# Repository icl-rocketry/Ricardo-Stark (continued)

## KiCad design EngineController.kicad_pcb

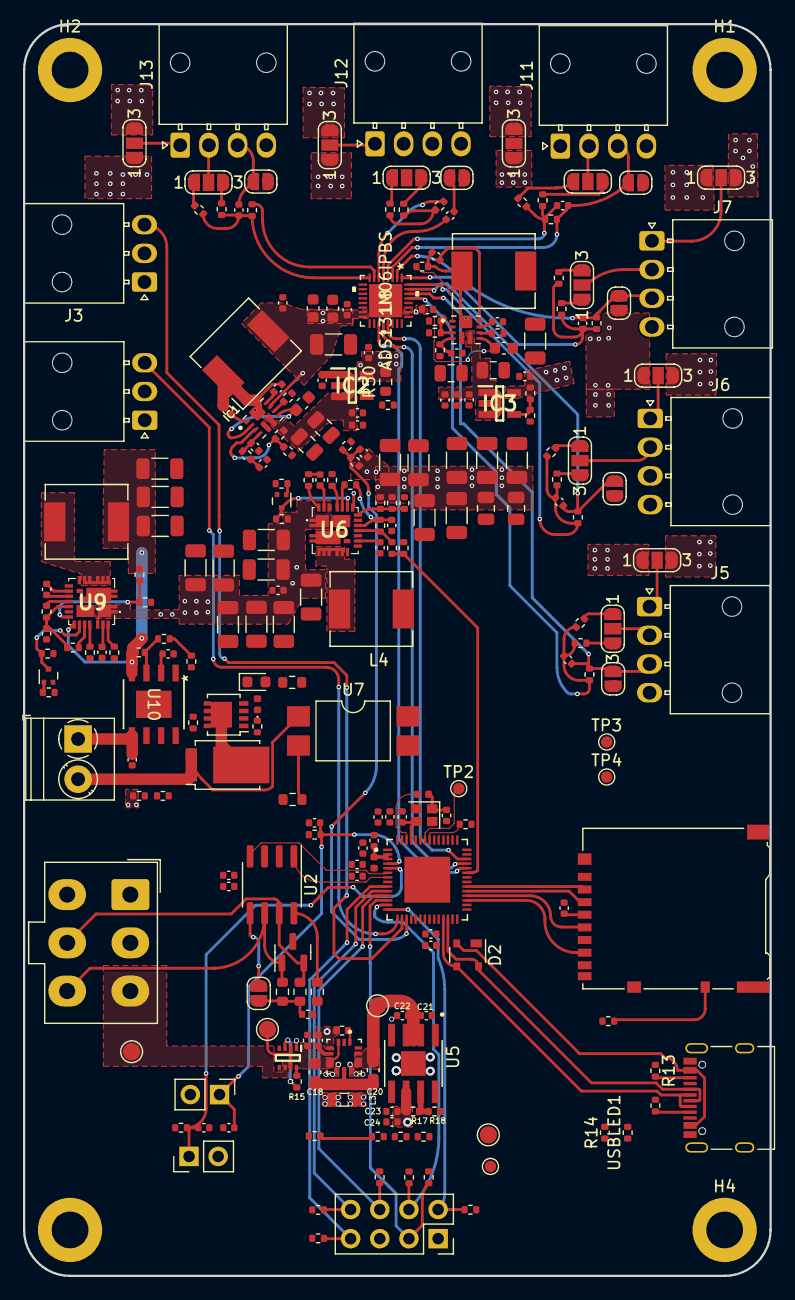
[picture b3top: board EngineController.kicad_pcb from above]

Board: 4 copper layers, 65.0 x 109.0 mm, 251 parts (0 on the bottom side), 150 nets.

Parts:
3V3LED1: BLUE_LED; R_0402_1005Metric
12VLED1: RED_LED; R_0402_1005Metric
BOOTJUMPER1: Conn_01x02_Male; PinHeader_1x02_P2.54mm_Vertical
C1, C15, C17, C21, C23, C66, C74: 10uF; C_0402_1005Metric
C2, C4, C7, C19, C25, C59, C68, C69, C71, C72: 1uF; C_0402_1005Metric
C3, C5, C6, C8, C10, C11, C24, C35, C46, C47, C91: 0.1uF; C_0402_1005Metric
C9, C48, C50, C51, C53, C54, C55: 10nF; C_0402_1005Metric
C12, C13: 11pF; C_0402_1005Metric
C14, C34, C62, C64, C67, C75, C80, C81: 100nF; C_0402_1005Metric
C16: 47nF; C_0402_1005Metric
C18, C49, C76: 10uF; C_0603_1608Metric
C20: 22uF; C_0603_1608Metric
C22, C26, C70: 4.7uF; C_0402_1005Metric
C27, C28, C29, C31, C33, C65, C85, C87, C89: 47uF; C_1206_3216Metric
C30, C32, C36, C38, C39, C40, C42, C43, C44, C45: DNP; C_1206_3216Metric
C37, C41: DNP; C_0805_2012Metric
C52: 100nF; C_0603_1608Metric
C56: 2.2uF; C_0603_1608Metric
C57: 180pF; C_0402_1005Metric
C58: 4.7nF; C_0402_1005Metric
C60, C61, C79: 22uF; C_0805_2012Metric
C63, C73: 2.2uF; C_0402_1005Metric
C77: 120pF; C_0402_1005Metric
C78: 2.2nF; C_0805_2012Metric
C82: 22uF; C_1206_3216Metric
C92: 2.2nF; C_0402_1005Metric
C93: 100uF; C_0402_1005Metric
D1: SM712_SOT23; SOT-23
D2: SP0503BAHT; SOT-143
D4: DST1550S; TO-277B
D6: RED_LED; LED_0603_1608Metric
ENJUMPER1: Conn_01x02_Male; PinHeader_1x02_P2.54mm_Vertical
Firing1: EMERALD_LED; LED_0402_1005Metric
H1, H2, H3, H4: MountingHole_Pad; MountingHole_3.2mm_M3_DIN965_Pad
IC1, IC4: TPS61089RNRR; IC_TPS61089RNRR
IC2, IC3: AP2205-W5-7; SOT95P282X145-5N
J1: RBUS; Molex_Mini-Fit_Jr_5566-06A_2x03_P4.20mm_Vertical
J2: USB_C_Receptacle_USB2.0; USB_C_Receptacle_Palconn_UTC16-G
J3: ServoCH1; Molex_Nano-Fit_105313-xx03_1x03_P2.50mm_Horizontal
J4: ServoCH2; Molex_Nano-Fit_105313-xx03_1x03_P2.50mm_Horizontal
J5, J6, J7, J11, J12, J13: 1053131104; Molex_Nano-Fit_105313-xx04_1x04_P2.50mm_Horizontal
J8: GPIO Breakout; PinSocket_2x04_P2.54mm_Vertical
J9: Micro_SD_Card_Det; microSD_HC_Hirose_DM3AT-SF-PEJM5
J10: Conn_01x02_Male; TerminalBlock_Phoenix_PT-1,5-2-3.5-H_1x02_P3.50mm_Horizontal
JP1: TermJP; SolderJumper-2_P1.3mm_Open_RoundedPad1.0x1.5mm
JP2, JP4, JP5, JP7, JP8, JP10, JP11, JP13, JP14, JP16, JP17, JP19: SolderJumper_3_Open; SolderJumper-3_P1.3mm_Open_RoundedPad1.0x1.5mm_NumberLabels
JP3, JP6, JP9, JP12, JP15, JP18: SolderJumper_2_Open; SolderJumper-2_P1.3mm_Open_RoundedPad1.0x1.5mm
L1: 2.0nH; L_0402_1005Metric
L2: 20nH; L_0402_1005Metric
L3: 1uH; L_0805_2012Metric
L4, L7: 3.3uH; IND_SRP6540-390M
L5, L6: SRR6038-5R0Y; IND_SRP6540-390M
Q1, Q3: SSM3K15AMFV,L3F; SOT-723
Q2: BUK9M11-40EX; LFPAK33
R1, R3: 10K; R_0402_1005Metric
R2, R4, R29: 470; R_0402_1005Metric
R5: 499R; R_0402_1005Metric
R6: 3k; R_0402_1005Metric
R7, R28: 1.5k; R_0402_1005Metric
R8: 2.2k; R_0402_1005Metric
R9: 0; R_0603_1608Metric
R10, R11: 60; R_0603_1608Metric
R12, R13, R14: 5.1k; R_0402_1005Metric
R15, R18, R19, R21, R27, R32, R35, R38, R41, R44, R47, R54, R57, R66, R67, R75, R86: 10k; R_0402_1005Metric
R16: 14k; R_0402_1005Metric
R17: 56k; R_0402_1005Metric
R20: 130k; R_0402_1005Metric
R22, R69: 2.2; R_0402_1005Metric
R23: 294k; R_0402_1005Metric
R24, R72: 1k; R_0402_1005Metric
R25, R73: 200k; R_0402_1005Metric
R26, R74: 100k; R_0402_1005Metric
R30, R33, R36, R39, R42, R52: 90k; R_0402_1005Metric
R31, R34, R37, R40, R43, R53: 31.7k; R_0402_1005Metric
R45: 17.4k; R_0402_1005Metric
R46: 1K; R_0402_1005Metric
R48: 127k; R_0402_1005Metric
R49: 50k; R_0402_1005Metric
R50: 152k; R_0603_1608Metric
R51: 301k; R_0402_1005Metric
R55: 51k; R_0402_1005Metric
R56: 0k; R_0402_1005Metric
R58: 190k; R_0402_1005Metric
R59, R60, R61, R62, R63, R64: DNP; R_0402_1005Metric
R65: 120; R_0402_1005Metric
R68: 120; R_0603_1608Metric
R70: 10k; R_0603_1608Metric
R76: 464K; R_0402_1005Metric
R77: 33.2K; R_0402_1005Metric
R78: 47.5K; R_0402_1005Metric
R79: 453; R_0402_1005Metric
R84: 18.7k; R_0402_1005Metric
R85: 2k; R_0402_1005Metric
R87: 475k; R_0402_1005Metric
R88: 287k; R_0402_1005Metric
TP1, TP2, TP3, TP4: TestPoint; TestPoint_Pad_D1.0mm
TP5, TP6, TP7, TP8: TestPoint; TestPoint_Pad_D1.5mm
TXLED1: GREEN_LED; R_0402_1005Metric
U1: ESP32-S3; QFN40P700X700X90-57N
U2: SN65HVD230; SOIC-8_3.9x4.9mm_P1.27mm
U3: LM66200DRLR; SOTFL50P160X60-8N
U4: MAX77827AEFD+T; CONV_MAX77827AEFD+T
U5: SC4215; SOIC127P599X175-9N
U6, U9: SiC437BED-T1-GE3; SiC437BEDT1GE3
U7: LTV-247; SMDIP-4_W9.53mm
U8: ADS131M06IPBS; ADS131M06IRSNR
U10: TPS259621DDAT; SO-PP-DDA-8_TEX
USBLED1: WHITE_LED; R_0402_1005Metric
Y1: R940000171; Crystal_SMD_2016-4Pin_2.0x1.6mm

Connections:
+3.3V: C1.1, C4.1, C5.1, C7.1, C9.1, C10.1, C11.1, C14.1, C15.1, C23.2, C24.2, C47.1, C49.1, C52.1, C64.1, C65.1, C71.1, C72.2, C81.1, C82.1, IC1.9 (VIN), IC4.9 (VIN), J8.5, J9.4 (VDD), L1.1, L5.1, L6.1, R1.1, R2.1, R3.1, R4.2, R17.1, R59.1, R60.1, R61.1, R62.1, R63.1, R64.1, R66.1, TP7.1, U1.20 (VDD3P3_RTC), U1.46 (VDD3P3_CPU), U1.55 (VDDA), U1.56 (VDDA), U2.3 (VCC), U5.6 (VOUT), U7.16, U8.15 (AVDD), U8.16 (SYNC/RESET), U8.26 (DVDD)
+5V: C63.1, IC2.5 (VOUT), JP4.1 (A), JP7.1 (A), JP10.1 (A), JP13.1 (A), JP16.1 (A), JP19.1 (A), R50.2
+6V: C29.1, C31.1, C33.1, C37.1, C39.1, C41.1, C43.1, C44.1, C45.1, C46.1, J3.2, J4.2, L4.1, R20.2, R23.2, R28.2, U6.18 (V_OUT)
+12V: C27.1, C28.1, C30.1, C32.1, C34.1, C36.1, C38.1, C40.1, C42.1, C73.1, IC3.5 (VOUT), J1.4, JP4.3 (B), JP7.3 (B), JP10.3 (B), JP13.3 (B), JP16.3 (B), JP19.3 (B), R6.1, R27.2, R56.2, U6.1 (V_IN_1), U6.2 (V_IN_2), U6.22 (VIN_1), U6.26 (VIN_2), U9.1 (V_IN_1), U9.2 (V_IN_2), U9.22 (VIN_1), U9.26 (VIN_2)
/ADS_CLK: U1.24 (GPIO18/ADC2_CH7/DAC_1), U8.23 (XTAL1/CLKIN)
/ADS_CS0: U1.27 (GPIO21), U8.17 (CS)
/BOOT: BOOTJUMPER1.1, C8.1, R3.2, U1.5 (GPIO0/BOOT)
/Boosts/FB_5V: IC1.3 (FB), R46.1, R47.2
/Boosts/FB_10V: IC4.3 (FB), R85.1, R86.2
/Boosts/LDO5.5V_IN: C59.1, C60.1, C61.1, C66.1, C67.1, IC1.6 (VOUT), IC2.1 (VIN), IC2.3 (EN), R46.2
/Boosts/LDO12V_IN: C69.1, C74.1, C75.1, C79.1, IC3.1 (VIN), IC3.3 (EN), IC4.6 (VOUT), R85.2
/Boosts/SW_5V: IC1.1 (FSW), R51.1
/Boosts/SW_10V: IC4.1 (FSW), R88.1
/BuckPGOOD: R7.1, R8.2, U1.37 (SPICLK_P/GPIO47)
/CAN+: D1.2 (A2), J1.5, R10.1, U2.7 (CANH)
/CAN-: D1.1 (A1), J1.6, R11.2, U2.6 (CANL)
/CAN-BUS/Vref: JP1.1 (A), U2.5 (Vref)
/CAN_RX: U1.6 (GPIO1/ADC1_CH0), U2.4 (R)
/CAN_TX: U1.7 (GPIO2/ADC1_CH1), U2.1 (D)
/CHIP_PU: C2.1, C3.1, ENJUMPER1.1, R1.2, U1.4 (CHIP_PU/RESET)
/Data+: D2.4 (K), J2.A6 (D+), J2.B6 (D+), TP4.1, U1.26 (GPIO20/USB_D+/ADC2_CH9)
/Data-: D2.3 (K), J2.A7 (D-), J2.B7 (D-), TP3.1, U1.25 (GPIO19/USB_D-/ADC2_CH8)
/HSPI_MISO: U1.39 (GPIO34), U8.20 (DOUT)
/HSPI_MOSI: U1.40 (GPIO35), U8.21 (DIN)
/HSPI_SCLK: U1.38 (GPIO33), U8.19 (SCLK)
/Power/BBIN: C17.1, C18.1, TP5.1, U3.2 (VOUT_1), U3.7 (VOUT_2), U4.3 (EN), U4.6 (IN)
/Power/BBOUT: C20.1, C21.1, C22.1, TP8.1, U4.11 (OUT), U4.13 (OUTS), U5.2 (EN), U5.3 (VIN)
/Power/BIAS: C19.1, U4.5 (BIAS)
/Power/FBIn: R17.2, R18.1, U5.7 (ADJ)
/Power/LX1: L3.1, U4.8 (LX1)
/Power/LX2: L3.2, U4.10 (LX2)
/Power/SEL: R16.1, U4.1 (SEL)
/Pyro/BOOT: C91.1, U9.23 (BOOT)
/Pyro/BUCKP_EN: Q3.1 (G), R72.2
/Pyro/Cont1: R68.1, U7.15
/Pyro/EFuse_In: C85.1, C87.1, C89.1, L7.1, R58.2, R76.2, U9.18 (V_OUT), U10.4 (IN)
/Pyro/EN: Q3.3 (D), R75.1, U9.19 (EN)
/Pyro/FB: R58.1, R67.2, U9.17 (FB)
/Pyro/Nuke 1: Firing1.2 (A), Q2.4 (G)
/Pyro/PGOOD: R57.2, U9.14 (P_GOOD)
/Pyro/PHASE: R69.1, U9.24 (PHASE)
/Pyro/PyroV: C93.2, J10.1, U10.5 (OUT)
/Pyro/SW: L7.2, U9.5 (SW_1), U9.6 (SW_2), U9.7 (SW_3), U9.8 (SW_4), U9.9 (SW_5), U9.30 (SW_6)
/Pyro/VDD: C68.2, R57.1, R73.2, U9.15 (VDD)
/RXD: TP2.1, U1.50 (U0RXD/PROG/GPIO44)
/Servo1PWM: J3.3, U1.16 (GPIO11/ADC2_CH0)
/Servo2PWM: J4.3, U1.15 (GPIO10/ADC1_CH9)
/ServoV_LOG: C46.2, R28.1, R29.2, U1.17 (GPIO12/ADC2_CH1)
/TXD: R5.1, TP1.1, TXLED1.1 (K)
/actuators/GPIO0: J8.2, R59.2, U1.14 (GPIO9/ADC1_CH8)
/actuators/GPIO1: J8.3, R60.2, U1.12 (GPIO7/ADC1_CH6)
/actuators/GPIO2: J8.4, R61.2, U1.13 (GPIO8/ADC1_CH7)
/actuators/GPIO3: J8.6, R62.2, U1.11 (GPIO6/ADC1_CH5)
/actuators/GPIO4: J8.7, R63.2, U1.9 (GPIO4/ADC1_CH3)
/actuators/GPIO5: J8.8, R64.2, U1.10 (GPIO5/ADC1_CH4)
/buckC/BOOT: C35.1, U6.23 (BOOT)
/buckC/BUCKC_EN: Q1.1 (G), R24.2, U1.18 (GPIO13/ADC2_CH2)
/buckC/EN: Q1.3 (D), R27.1, U6.19 (EN)
/buckC/FB: R20.1, R21.2, R23.1, U6.17 (FB)
/buckC/PGOOD: R7.2, R19.2, U6.14 (P_GOOD)
/buckC/PHASE: R22.1, U6.24 (PHASE)
/buckC/SW: L4.2, U6.5 (SW_1), U6.6 (SW_2), U6.7 (SW_3), U6.8 (SW_4), U6.9 (SW_5), U6.30 (SW_6)
/buckC/VDD: C25.2, R19.1, R25.2, U6.15 (VDD)
/microSD/SD1_DET: J9.10 (DET_A), R66.2
/microSD/VSPI_MISO: J9.7 (DAT0), U1.31 (SPIWP/GPIO28)
/microSD/VSPI_SCLK: J9.5 (CLK), U1.32 (SPICS0/GPIO29)
/pressure_sensor/AIN0N: C48.2, J5.3, JP3.2 (B), R32.2, U8.30 (AIM0N)
/pressure_sensor/AIN0P: C48.1, R30.2, R31.2, R32.1, U8.29 (AIN0P)
/pressure_sensor/AIN1N: C50.2, J6.3, JP6.2 (B), R35.2, U8.31 (AIN1N)
/pressure_sensor/AIN1P: C50.1, R33.2, R34.2, R35.1, U8.32 (AIN1P)
/pressure_sensor/AIN2N: C51.2, J7.3, JP9.2 (B), R38.2, U8.2 (AIN2N)
/pressure_sensor/AIN2P: C51.1, R36.2, R37.2, R38.1, U8.1 (AIN2P)
/pressure_sensor/AIN3N: C53.2, J11.3, JP12.2 (B), R41.2, U8.3 (AIN3N)
/pressure_sensor/AIN3P: C53.1, R39.2, R40.2, R41.1, U8.4 (AIN3P)
/pressure_sensor/AIN4N: C54.2, J12.3, JP15.2 (B), R44.2, U8.6 (AIN4N)
/pressure_sensor/AIN4P: C54.1, R42.2, R43.2, R44.1, U8.5 (AIN4P)
/pressure_sensor/AIN5N: C55.2, J13.3, JP18.2 (B), R54.2, U8.7 (AIN5N)
/pressure_sensor/AIN5P: C55.1, R52.2, R53.2, R54.1, U8.8 (AIN5P)
GND: 3V3LED1.1 (K), 12VLED1.1 (K), BOOTJUMPER1.2, C1.2, C2.2, C3.2, C4.2, C5.2, C6.2, C7.2, C8.2, C9.2, C10.2, C11.2, C12.2, C13.2, C14.2, C15.2, C16.2, C17.2, C18.2, C19.2, C20.2, C21.2, C22.2, C23.1, C24.1, C25.1, C26.1, C27.2, C28.2, C29.2, C30.2, C31.2, C32.2, C33.2, C34.2, C36.2, C37.2, C38.2, C39.2, C40.2, C41.2, C42.2, C43.2, C44.2, C45.2, C47.2, C49.2, C52.2, C56.2, C57.2, C58.2, C59.2, C60.2, C61.2, C63.2, C64.2, C65.2, C66.2, C67.2, C68.1, C69.2, C70.1, C71.2, C72.1, C73.2, C74.2, C75.2, C76.2, C77.2, C78.2, C79.2, C81.2, C82.2, C85.2, C87.2, C89.2, C92.1, C93.1, D1.3 (common), D2.1 (A), D6.1 (K), ENJUMPER1.2, H1.1, H2.1, H3.1, H4.1, IC1.5 (GND), IC2.2 (GND), IC3.2 (GND), IC4.5 (GND), J1.1, J1.2, J2.A1 (GND), J2.A12 (GND), J2.B1 (GND), J2.B12 (GND), J2.S1 (SHIELD), J3.1, J4.1, J5.4, J6.4, J7.4, J8.1, J9.6 (VSS), J9.9 (DET_B), J9.11 (SHIELD), J11.4, J12.4, J13.4, JP3.1 (A), JP6.1 (A), JP9.1 (A), JP12.1 (A), JP15.1 (A), JP18.1 (A), Q1.2 (S), Q2.1 (S), Q2.2 (S), Q2.3 (S), Q3.2 (S), R8.1, R9.2, R12.2, R13.1, R16.2, R18.2, R21.1, R24.1, R26.2, R29.1, R47.1, R48.1, R49.1, R55.1, R65.2, R67.1, R70.2, R72.1, R74.2, R78.2, R86.1, R87.1, U1.57 (GND), U2.2 (GND), U3.1 (GND_1), U3.4 (~ON), U3.5 (GND_2), U4.4 (AGND), U4.9 (PGND), U5.8 (GND), U5.9 (GND), U6.3 (P_GND_1), U6.4 (P_GND_2), U6.13 (P_GND_3), U6.16 (A_GND), U6.25 (AGND), U6.27 (PGND), U6.29 (P_GND_4), U8.13 (AGND), U8.25 (DGND), U9.3 (P_GND_1), U9.4 (P_GND_2), U9.13 (P_GND_3), U9.16 (A_GND), U9.25 (AGND), U9.27 (PGND), U9.29 (P_GND_4), U10.1 (GND), U10.EPAD (GND), USBLED1.1 (K), Y1.2, Y1.4
unnamed: 3V3LED1.2 (A), R4.1
unnamed: 12VLED1.2 (A), R6.2
unnamed: C6.1, L1.2, U1.2 (VDD3P3), U1.3 (VDD3P3)
unnamed: C13.1, L2.2, Y1.1
unnamed: C35.2, R22.2
unnamed: C58.1, R45.2
unnamed: C78.1, R84.2
unnamed: C91.2, R69.2
unnamed: D4.3 (K), Q2.5 (D)
unnamed: D6.2 (A), R68.2
unnamed: Firing1.1 (K), R65.1
unnamed: C62.1, IC1.10 (BOOT)
unnamed: C57.1, IC1.4 (COMP), R45.1
unnamed: C56.1, IC1.2 (VCC), IC1.7 (EN)
unnamed: IC1.8 (ILIM), R48.2
unnamed: C62.2, IC1.11 (SW), L5.2, R51.2
unnamed: IC2.4 (ADJ/NC), R49.2, R50.1
unnamed: IC3.4 (ADJ/NC), R55.2, R56.1
unnamed: C80.1, IC4.10 (BOOT)
unnamed: C77.1, IC4.4 (COMP), R84.1
unnamed: C76.1, IC4.2 (VCC), IC4.7 (EN)
unnamed: IC4.8 (ILIM), R87.2
unnamed: C80.2, IC4.11 (SW), L6.2, R88.2
unnamed: J2.A5 (CC1), R12.1
unnamed: J2.B5 (CC2), R13.2
unnamed: D4.1 (A), D4.2 (A), J10.2, U7.1
unnamed: C16.1, JP1.2 (B), R10.2, R11.1
unnamed: JP2.1 (A), R31.1
unnamed: JP2.3 (B), R30.1
unnamed: J5.2, JP2.2 (C)
unnamed: J5.1, JP4.2 (C)
unnamed: JP5.1 (A), R34.1
unnamed: JP5.3 (B), R33.1
unnamed: J6.2, JP5.2 (C)
unnamed: J6.1, JP7.2 (C)
unnamed: JP8.1 (A), R37.1
unnamed: JP8.3 (B), R36.1
unnamed: J7.2, JP8.2 (C)
unnamed: J7.1, JP10.2 (C)
unnamed: JP11.1 (A), R40.1
unnamed: JP11.3 (B), R39.1
unnamed: J11.2, JP11.2 (C)
unnamed: J11.1, JP13.2 (C)
unnamed: JP14.1 (A), R43.1
unnamed: JP14.3 (B), R42.1
unnamed: J12.2, JP14.2 (C)
unnamed: J12.1, JP16.2 (C)
unnamed: JP17.1 (A), R53.1
unnamed: JP17.3 (B), R52.1
unnamed: J13.2, JP17.2 (C)
unnamed: J13.1, JP19.2 (C)
unnamed: R70.1, U7.2
unnamed: R2.2, TXLED1.2 (A)
unnamed: R5.2, U1.49 (U0TXD/PROG/GPIO43)
unnamed: C12.1, U1.53 (XTAL_N), Y1.3
unnamed: L2.1, U1.54 (XTAL_P)
unnamed: R9.1, U2.8 (Rs)
unnamed: R15.2, U3.8 (ST)
unnamed: R25.1, U6.20 (MODE_2)
unnamed: C26.2, U6.12 (V_DRV)
unnamed: R26.1, U6.21 (_MODE_1)
unnamed: R73.1, U9.20 (MODE_2)
unnamed: C70.2, U9.12 (V_DRV)
unnamed: R74.1, U9.21 (_MODE_1)
unnamed: R76.1, R77.2, U10.3 (EN/UVLO)
unnamed: R79.1, U10.7 (ILM)
unnamed: R77.1, R78.1, R79.2, U10.8 (OVLO/OVCSEL)
unnamed: C92.2, U10.2 (dVdt)
unnamed: R14.2, USBLED1.2 (A)
RBUS_uC_V: J1.3, TP6.1, U3.6 (VIN2)
VBUS: D2.2 (K), J2.A4 (VBUS), J2.A9 (VBUS), J2.B4 (VBUS), J2.B9 (VBUS), R14.1, R15.1, U3.3 (VIN1)

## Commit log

2023-11-11 Initial template
2023-11-11 Engine Controller Board: Added in Buck
    Added in buck for chad and modified resistors to have output of 7.4V and 6V instead of 8.4V
2023-11-18 Xavier: Updated Engine Controller
    Added in the actuators
2023-11-21 Engine Controller: Added in ads and pressure sensor
    Circuit for both 5v and 10v
2024-01-23 Completed schematics
2024-02-06 Xavier: Modified ADS board
    Pressure Sensor ADS board reduced to ADS131M03 with 3 channels for the 3 pressure sensors
2024-03-09 Finished schematic
2024-03-09 Forgot Pyro
2024-03-10 forgot sd card and added ads chip
2024-03-16 Schematic done, components layed out, sensors wired up
2024-03-17 Wired up more stuff
2024-03-17 All wired up
2024-03-18 Lol 12V zone priority needs changing but silkscreen looks nice
2024-03-26 v1.2
2024-03-30 More Based
2024-03-30 Last commit wasnt based enough, forgot analogue ground isolation
2024-03-31 Forgot Teardrops and added dimensions
2024-03-31 added a via and felt like pushing
2024-03-31 Lol pyro buck out was shorting straight to ground
2024-03-31 added pyro buck caps
2024-04-03 changed led resistances
2024-04-05 fixed crystal via stitching
2024-04-14 Most Review 1 changes made
2024-04-19 Review 1 Changes Complete
2024-04-21 Fixed USB tracks
2024-05-14 Take 3
2024-05-15 Sized sensor resistors and more routing
2024-05-20 added silkscreen
2024-05-21 added more silkscreen
2024-05-24 improved pyro output cap placement so technical lead approves
2024-05-30 review changes
2024-06-01 5v breakout
2024-06-01 fixed drc
2024-06-06 fixed via
2024-06-06 fixed another via
2024-06-06 saved leds from blowing
2024-06-07 changed inductor footprint
2024-07-17 artem big brain moment
2024-07-25 reshuffled layout
2024-07-25 Added sensors
2024-07-25 Kiran Review Changes
2024-07-28 more changes
2024-07-30 added 30V input caps
2024-08-01 changed boost out
2024-08-03 added 3d connectors
2024-08-04 changed sd mosfet footprint
2024-08-04 review 3 changes
2024-08-04 tcmt1109 instead of ltv
2024-08-07 Andrei review changes
2024-08-08 made it look nicer
2024-08-08 fixed sd mosfet footprint
2024-08-12 Changed sd card holder
2024-08-12 LDO 5V resistor change
2024-08-16 Fixed sd det
2024-08-24 Added Firmware folder
2024-08-24 Revert "Added Firmware folder"
    This reverts commit db9fcbd56da78149f63fb568c453a94413145aad.
2024-08-24 Submodules
2024-08-24 Arduino submodule
2024-08-24 Added Firmware
2024-08-24 Removed submodule Firmware/components/arduino-esp32
2024-09-06 Engine Controller added
2024-09-07 Removed circular dependency error
2024-09-07 Engine commit
2024-09-07 Changed controlled state
2024-09-07 push
2024-09-07 Added servos to telem packet
2024-09-08 modification for coldflow
2024-09-08 updated for flight quali
2024-09-13 Ox FF bug fix
2024-09-15 Flight Qualification Hotfire
2024-09-23 Cleaning up controlled state
2024-09-23 Valve angles chosen from vector
2024-09-27 Updated arming logic
2024-10-27 Nimbus 24 Engine Controller
2024-11-20 Passing engine test params as command arguement
2024-11-30 Added engine test params to update
2024-11-30 Igniter Test Controller
2024-11-30 Added abort
2024-11-30 valve lag bug fix
2024-12-04 Final Igniter Controller
2024-12-12 Refactored sensor handling + OF calc
2024-12-15 Hopper Engine hotfire
2024-12-15 Added fuel lead and ramp up
2024-12-15 added n2 shutdown
2024-12-15 arg 0
2024-12-15 might have fixed fuel lead
2024-12-15 removed valve limits
2024-12-15 Bug fixes + cleanup
2024-12-16 longer pre angle
2025-01-17 updated sensors and other stuff
2025-02-02 rearranged comps
2025-02-22 coldflow
2025-02-22 uncommented abort and trying some stuff
2025-02-22 updated sensor handler config
2025-03-18 Latest hopper engine test firmware
2025-03-27 Finished Boosts and Sensors
2025-03-28 Updated SD card, GPIOs, CAN, Power section
2025-03-29 Routed Switch and Servo driver subsystems
2025-03-31 Added actuators and I2C bus
2025-04-03 Almost done
2025-04-05 Fixed all DRC Errors
2025-04-05 Updated Silkcreen and test points
2025-04-06 v2 Ready for Review
2025-04-11 Most Review Changes
2025-04-12 Remaining Review Changes
2025-04-12 Forgot switch enable DNP pull up
2025-04-14 can termination upgrade
2025-04-18 Cosmetic Changes
2025-04-25 6 layer and production files
2025-05-17 v2 pins
2025-05-21 logframe edit
2025-05-22 SD Card bug fix
2025-08-27 updated librrc submodules
2025-08-27 updated to new idf, added pca support pyro continuity
2025-08-30 fixed LocalPWM old API usage
2025-08-30 configured and enabled pyro power switch
2025-08-31 Linear Interpolation for engine startup ramp + arming bug fix
2025-08-31 Updated ereg shutdown command params
2025-08-31 Corrected ereg shutdown
2025-09-02 Pluto flight qualification
2025-10-07 Added TC to sensor handler and shortened telem packet
2025-11-20 Pluto Flight Firmware
2026-03-24 Replaced PicoClasp with nanofits
2026-03-31 Solenoid Feature and minor changes
2026-05-12 Added flyback on pyro channel
2026-06-08 quick changes before silwood
2026-06-24 schematic reformatting and bom consolidation
2026-06-24 changed fp
